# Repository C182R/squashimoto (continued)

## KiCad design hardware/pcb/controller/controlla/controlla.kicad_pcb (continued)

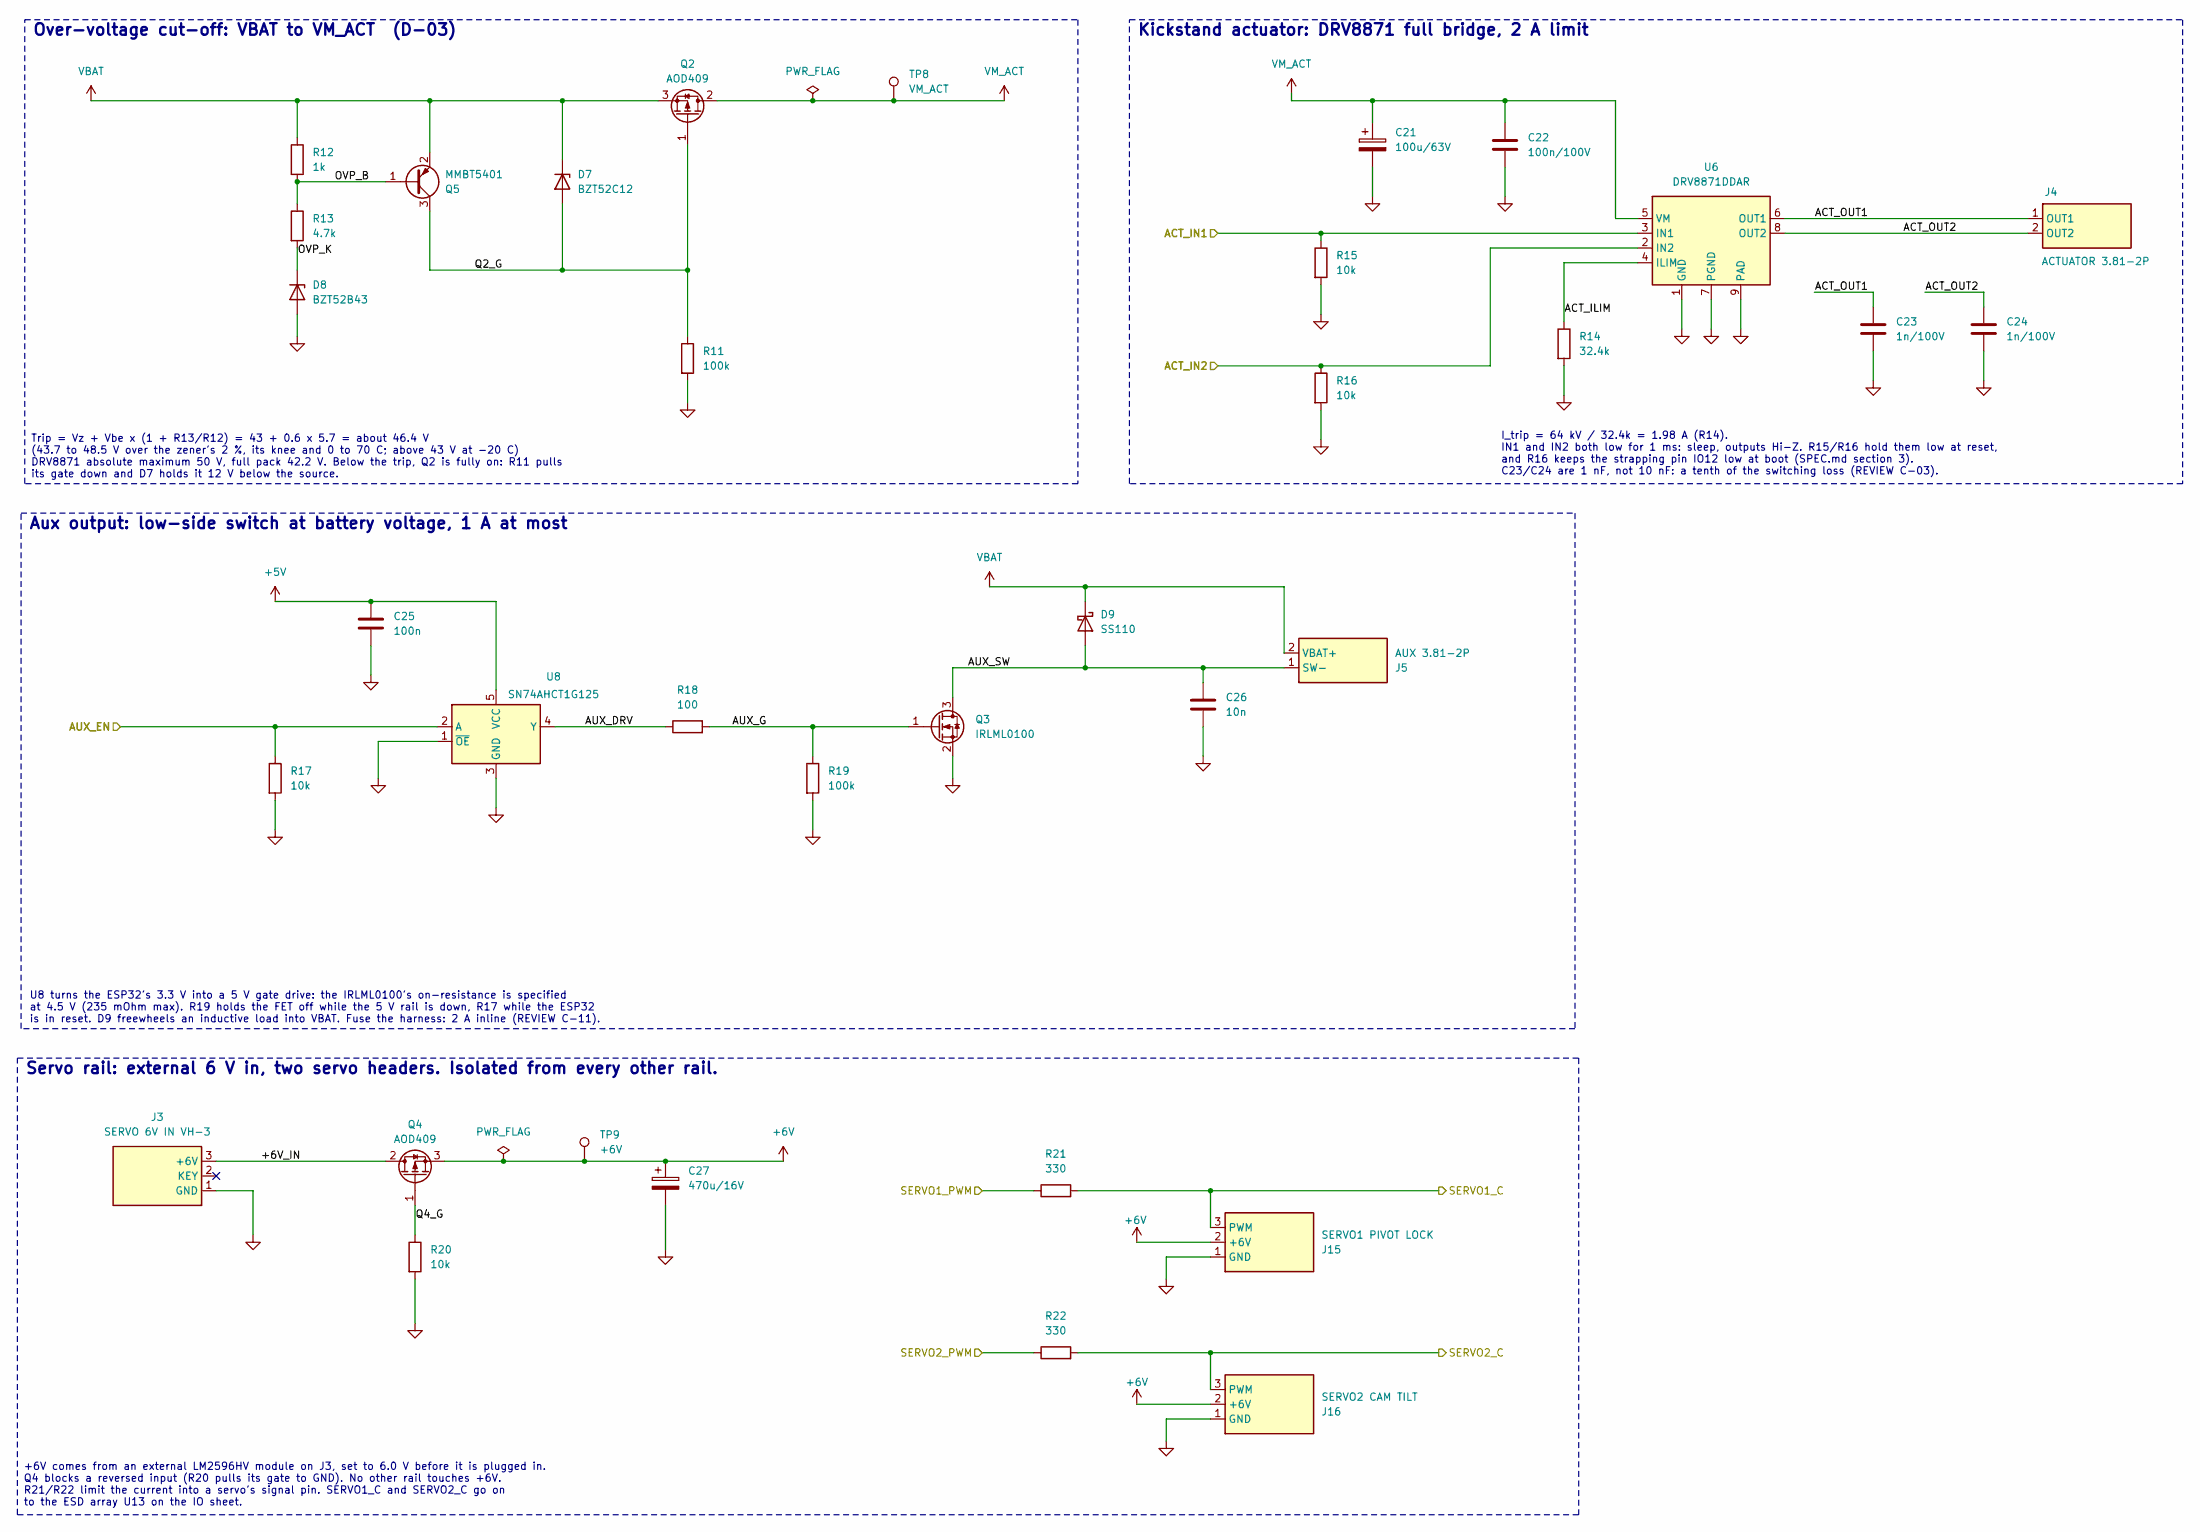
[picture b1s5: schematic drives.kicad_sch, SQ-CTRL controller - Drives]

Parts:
C21: 100u/63V; CP_Radial_D8.0mm_P3.50mm; MPN 63ZLH100MEFC8X16; LCSC C88747
C22: 100n/100V; C_0603_1608Metric; MPN TCC0603X7R104K101CT; LCSC C696916
C23, C24: 1n/100V; C_0603_1608Metric; MPN CC0603KRX7R0BB102; LCSC C106247
C25: 100n; C_0603_1608Metric; MPN CC0603KRX7R9BB104; LCSC C14663
C26: 10n; C_0603_1608Metric; MPN CC0603KRX7R0BB103; LCSC C107059
C27: 470u/16V; CP_Radial_D8.0mm_P3.50mm; MPN SHG470UF16V03EC0549; LCSC C2943989
D7: BZT52C12; D_SOD-123; MPN BZT52C12; LCSC C173429
D8: BZT52B43; D_SOD-123; MPN BZT52B43; LCSC C699127
D9: SS110; D_SMA; MPN SS110; LCSC C2482
J3: SERVO 6V IN VH-3; JST_VH_B3P-VH_1x03_P3.96mm_Vertical; MPN B3P-VH(LF)(SN); LCSC C160316
J4: ACTUATOR 3.81-2P; PhoenixContact_MC_1,5_2-G-3.81_1x02_P3.81mm_Horizontal; MPN KF2EDGR-3.81-2P; LCSC C441182
J5: AUX 3.81-2P; PhoenixContact_MC_1,5_2-G-3.81_1x02_P3.81mm_Horizontal; MPN KF2EDGR-3.81-2P; LCSC C441182
J15: SERVO1 PIVOT LOCK; PinHeader_1x03_P2.54mm_Vertical; MPN KH-2.54PH180-1X3P-L11.5; LCSC C2932698
J16: SERVO2 CAM TILT; PinHeader_1x03_P2.54mm_Vertical; MPN KH-2.54PH180-1X3P-L11.5; LCSC C2932698
Q2, Q4: AOD409; TO-252-2; MPN AOD409; LCSC C36220
Q3: IRLML0100; SOT-23; MPN IRLML0100TRPBF; LCSC C53658
Q5: MMBT5401; SOT-23; MPN MMBT5401(RANGE:200-300); LCSC C8326
R11, R19: 100k; R_0603_1608Metric; MPN 0603WAF1003T5E; LCSC C25803
R12: 1k; R_0603_1608Metric; MPN 0603WAF1001T5E; LCSC C21190
R13: 4.7k; R_0603_1608Metric; MPN 0603WAF4701T5E; LCSC C23162
R14: 32.4k; R_0603_1608Metric; MPN 0603WAF3242T5E; LCSC C13187
R15, R16, R17, R20: 10k; R_0603_1608Metric; MPN 0603WAF1002T5E; LCSC C25804
R18: 100; R_0603_1608Metric; MPN 0603WAF1000T5E; LCSC C22775
R21, R22: 330; R_0603_1608Metric; MPN 0603WAF3300T5E; LCSC C23138
TP8: VM_ACT; TestPoint_Pad_D1.5mm
TP9: +6V; TestPoint_Pad_D1.5mm
U6: DRV8871DDAR; HSOP-8-1EP_3.9x4.9mm_P1.27mm_EP2.41x3.1mm; MPN DRV8871DDAR; LCSC C75864
U8: SN74AHCT1G125; SOT-23-5; MPN SN74AHCT1G125DBVR; LCSC C7484

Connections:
+5V: C25.1, U8.5 (VCC); also elsewhere on the board
+6V: C27.1, J15.2 (+6V), J16.2 (+6V), Q4.3 (S), TP9.1 (1_1)
/MCU/ACT_IN1: R15.1, U6.3 (IN1); also elsewhere on the board
/MCU/ACT_IN2: R16.1, U6.2 (IN2); also elsewhere on the board
/MCU/AUX_EN: R17.1, U8.2 (A); also elsewhere on the board
/MCU/SERVO1_PWM: R21.1; also elsewhere on the board
/MCU/SERVO2_PWM: R22.1; also elsewhere on the board
/drives/+6V_IN: J3.3 (+6V), Q4.2 (D)
/drives/ACT_ILIM: R14.1, U6.4 (ILIM)
/drives/ACT_OUT1: C23.1, J4.1 (OUT1), U6.6 (OUT1)
/drives/ACT_OUT2: C24.1, J4.2 (OUT2), U6.8 (OUT2)
/drives/AUX_DRV: R18.1, U8.4 (Y)
/drives/AUX_G: Q3.1 (G), R18.2, R19.1
/drives/AUX_SW: C26.1, D9.2 (A), J5.1 (SW-), Q3.3 (D)
/drives/OVP_B: Q5.1 (B), R12.2, R13.1
/drives/OVP_K: D8.1 (K), R13.2
/drives/Q2_G: D7.2 (A), Q2.1 (G), Q5.3 (C), R11.1
/drives/Q4_G: Q4.1 (G), R20.1
/drives/SERVO1_C: J15.3 (PWM), R21.2; also elsewhere on the board
/drives/SERVO2_C: J16.3 (PWM), R22.2; also elsewhere on the board
GND: C21.2, C22.2, C23.2, C24.2, C25.2, C26.2, C27.2, D8.2 (A), J3.1 (GND), J15.1 (GND), J16.1 (GND), Q3.2 (S), R11.2, R14.2, R15.2, R16.2, R17.2, R19.2, R20.2, U6.1 (GND), U6.7 (PGND), U6.9 (PAD), U8.1 (~OE), U8.3 (GND); also elsewhere on the board
VBAT: D7.1 (K), D9.1 (K), J5.2 (VBAT+), Q2.3 (S), Q5.2 (E), R12.1; also elsewhere on the board
VM_ACT: C21.1, C22.1, Q2.2 (D), TP8.1 (1_1), U6.5 (VM)

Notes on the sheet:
Servo rail: external 6 V in, two servo headers. Isolated from every other rail.
Aux output: low-side switch at battery voltage, 1 A at most
I_trip = 64 kV / 32.4k = 1.98 A (R14). IN1 and IN2 both low for 1 ms: sleep, outputs Hi-Z. R15/R16 hold them low at reset, and R16 keeps the strapping pin IO12 low at boot (SPEC.md section 3). C23/C24 are 1 nF, not 10 nF: a tenth of the switching loss (REVIEW C-03).
Kickstand actuator: DRV8871 full bridge, 2 A limit
U8 turns the ESP32's 3.3 V into a 5 V gate drive: the IRLML0100's on-resistance is specified at 4.5 V (235 mOhm max). R19 holds the FET off while the 5 V rail is down, R17 while the ESP32 is in reset. D9 freewheels an inductive load into VBAT. Fuse the harness: 2 A inline (REVIEW C-11).
Trip = Vz + Vbe x (1 + R13/R12) = 43 + 0.6 x 5.7 = about 46.4 V (43.7 to 48.5 V over the zener's 2 %, its knee and 0 to 70 C; above 43 V at -20 C) DRV8871 absolute maximum 50 V, full pack 42.2 V. Below the trip, Q2 is fully on: R11 pulls its gate down and D7 holds it 12 V below the source.
Over-voltage cut-off: VBAT to VM_ACT (D-03)
+6V comes from an external LM2596HV module on J3, set to 6.0 V before it is plugged in. Q4 blocks a reversed input (R20 pulls its gate to GND). No other rail touches +6V. R21/R22 limit the current into a servo's signal pin. SERVO1_C and SERVO2_C go on to the ESD array U13 on the IO sheet.

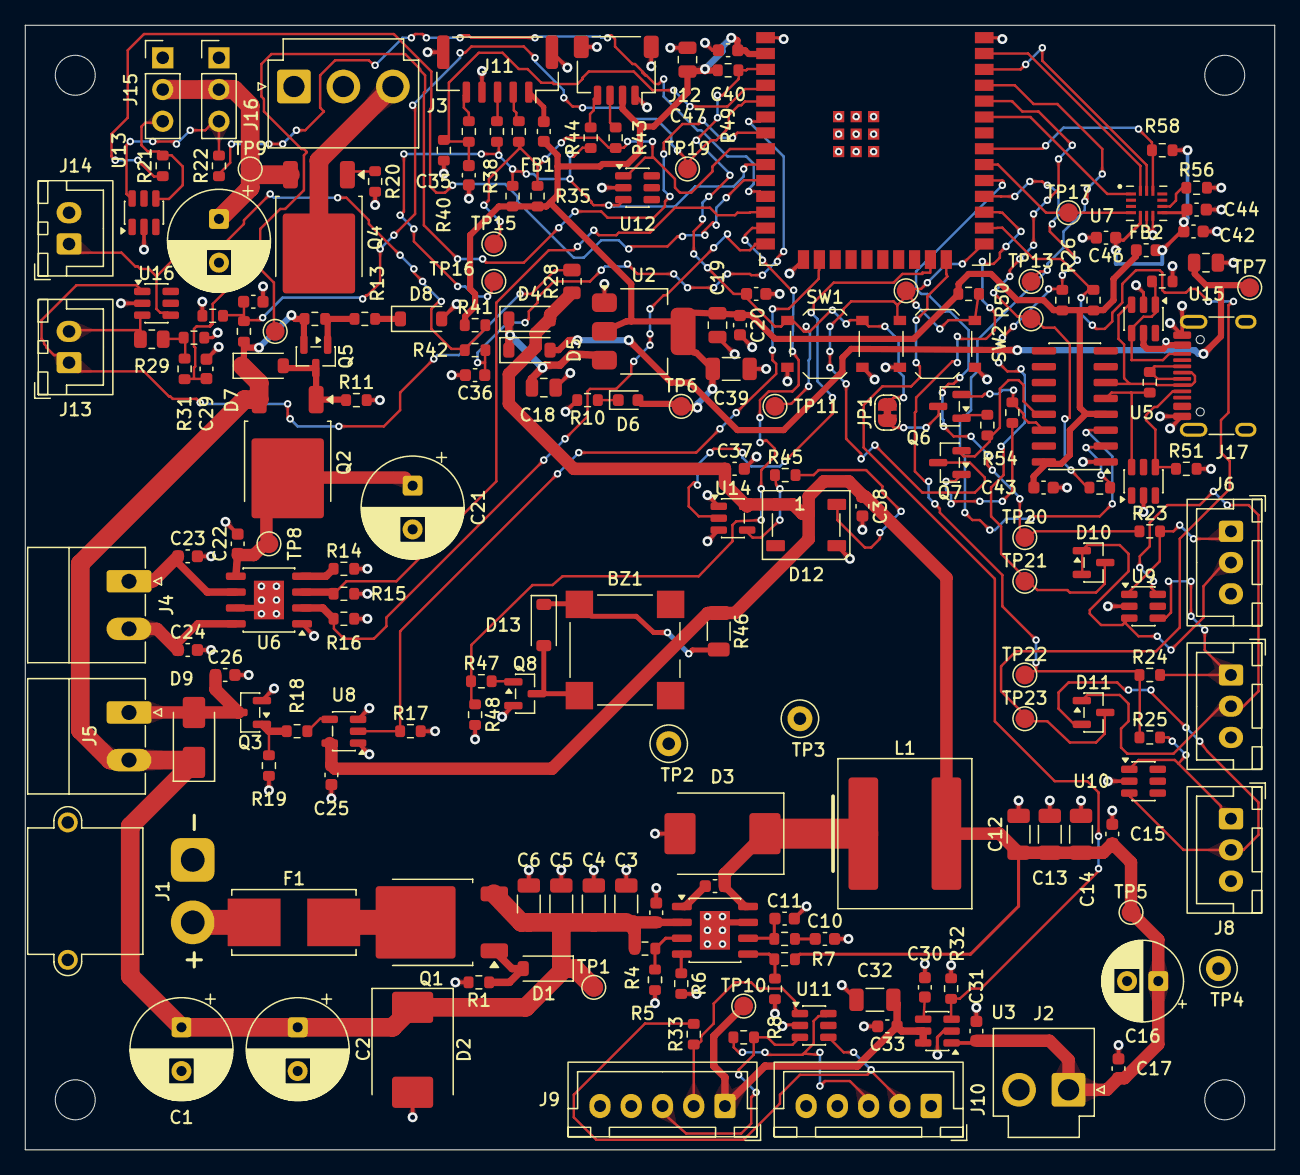
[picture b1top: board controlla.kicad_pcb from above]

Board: 4 copper layers, 100.0 x 90.0 mm, 193 parts (0 on the bottom side), 100 nets.

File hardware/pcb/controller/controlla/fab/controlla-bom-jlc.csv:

"Comment","Designator","Footprint","LCSC Part #"
"MLT-8530","BZ1","squashimoto:Buzzer_Huaneng_MLT-8530","C94599"
"100u/63V","C1,C2,C21","squashimoto:CP_Radial_D8.0mm_P3.50mm","C88747"
"2.2u/100V","C3,C4,C5,C6","squashimoto:C_1206_3216Metric","C577211"
"100n/100V","C7,C22","squashimoto:C_0603_1608Metric","C696916"
"100n","C8,C9,C15,C17,C20,C25,C29,C33,C36,C37,C38,C40,C43,C44","squashimoto:C_0603_1608Metric","C14663"
"10n","C10,C26,C35,C46","squashimoto:C_0603_1608Metric","C107059"
"100p","C11","squashimoto:C_0603_1608Metric","C14858"
"22u","C12,C13,C14,C32,C39","squashimoto:C_1206_3216Metric","C12891"
"470u/10V poly","C16","squashimoto:CP_Radial_D6.3mm_P2.50mm","C698160"
"10u","C18,C19,C42,C47","squashimoto:C_0805_2012Metric","C15850"
"1n/100V","C23,C24","squashimoto:C_0603_1608Metric","C106247"
"470u/16V","C27","squashimoto:CP_Radial_D8.0mm_P3.50mm","C2943989"
"2.2n","C30","squashimoto:C_0603_1608Metric","C16033"
"1u","C31,C41","squashimoto:C_0603_1608Metric","C15849"
"2.2u","C45","squashimoto:C_0603_1608Metric","C23630"
"BZT52C12","D1,D7","squashimoto:D_SOD-123","C173429"
"SMDJ45A","D2","squashimoto:D_SMC","C49066976"
"SK1010C","D3","squashimoto:D_SMC","C65020"
"B5819W","D4,D5","squashimoto:D_SOD-123","C64885"
"red","D6","squashimoto:LED_0603_1608Metric","C2286"
"BZT52B43","D8","squashimoto:D_SOD-123","C699127"
"SS110","D9","squashimoto:D_SMA","C2482"
"BAT54A","D10,D11","squashimoto:SOT-23","C181199"
"WS2812B","D12","squashimoto:LED_WS2812B_PLCC4_5.0x5.0mm_P3.2mm","C2843785"
"1N4148W","D13","squashimoto:D_SOD-123","C81598"
"7A 0154007.DRT","F1","squashimoto:Fuseholder_Littelfuse_Nano2_154x","C2760740"
"600R","FB1,FB2","squashimoto:L_0603_1608Metric","C19330"
"XT30PW-M","J1","squashimoto:AMASS_XT30PW-M_1x02_P2.50mm_Horizontal","C431092"
"PI 5V VH-2","J2","squashimoto:JST_VH_B2P-VH_1x02_P3.96mm_Vertical","C160315"
"SERVO 6V IN VH-3","J3","squashimoto:JST_VH_B3P-VH_1x03_P3.96mm_Vertical","C160316"
"ACTUATOR 3.81-2P,AUX 3.81-2P","J4,J5","squashimoto:PhoenixContact_MC_1,5_2-G-3.81_1x02_P3.81mm_Horizontal","C441182"
"UART FRONT L,UART FRONT R,UART REAR","J6,J7,J8","squashimoto:JST_XH_B3B-XH-A_1x03_P2.50mm_Vertical","C144394"
"LIDAR USB ADAPTER XH-5,LIDAR XH-5","J9,J10","squashimoto:JST_XH_B5B-XH-A_1x05_P2.50mm_Vertical","C157991"
"ENCODER GH-5","J11","squashimoto:JST_GH_SM05B-GHS-TB_1x05-1MP_P1.25mm_Horizontal","C189896"
"I2C SPARE SH-4","J12","squashimoto:JST_SH_SM04B-SRSS-TB_1x04-1MP_P1.00mm_Horizontal","C160404"
"BATT NTC 10k,E-STOP NC","J13,J14","squashimoto:JST_XH_B2B-XH-A_1x02_P2.50mm_Vertical","C158012"
"SERVO1 PIVOT LOCK,SERVO2 CAM TILT","J15,J16","squashimoto:PinHeader_1x03_P2.54mm_Vertical","C2932698"
"USB-C TYPE-C-31-M-12","J17","squashimoto:USB_C_Receptacle_HRO_TYPE-C-31-M-12","C165948"
"10uH XAL1010","L1","squashimoto:L_Coilcraft_XAL1010-XXX","C6358489"
"AOD409","Q1,Q2,Q4","squashimoto:TO-252-2","C36220"
"IRLML0100","Q3","squashimoto:SOT-23","C53658"
"MMBT5401","Q5","squashimoto:SOT-23","C8326"
"SS8050","Q6,Q7","squashimoto:SOT-23","C2150"
"AO3400A","Q8","squashimoto:SOT-23","C20917"
"100k","R1,R2,R11,R19,R39","squashimoto:R_0603_1608Metric","C25803"
"5.1k","R3,R51,R52","squashimoto:R_0603_1608Metric","C23186"
"732k","R4","squashimoto:R_0603_1608Metric","C23239"
"33.2k","R5","squashimoto:R_0603_1608Metric","C23003"
"240k","R6","squashimoto:R_0603_1608Metric","C4197"
"53.6k","R7","squashimoto:R_0603_1608Metric","C23074"
"10k","R8,R15,R16,R17,R20,R31,R32,R48,R49,R50,R54,R55,R56,R58","squashimoto:R_0603_1608Metric","C25804"
"16.2k","R9","squashimoto:R_0603_1608Metric","C22885"
"1k","R10,R12,R23,R24,R25,R30,R42","squashimoto:R_0603_1608Metric","C21190"
"4.7k","R13,R26,R27","squashimoto:R_0603_1608Metric","C23162"
"32.4k","R14","squashimoto:R_0603_1608Metric","C13187"
"100","R18,R37,R38,R43,R44,R47","squashimoto:R_0603_1608Metric","C22775"
"330","R21,R22,R45","squashimoto:R_0603_1608Metric","C23138"
"330","R28,R29","squashimoto:R_0805_2012Metric","C17630"
"470","R33,R53","squashimoto:R_0603_1608Metric","C23179"
"2.2k","R34,R35,R36","squashimoto:R_0603_1608Metric","C4190"
"220k","R40","squashimoto:R_0603_1608Metric","C22961"
"20k","R41","squashimoto:R_0603_1608Metric","C4184"
"10","R46","squashimoto:R_1206_3216Metric","C17903"
"0","R59","squashimoto:R_0603_1608Metric","C21189"
"BOOT,RESET","SW1,SW2","squashimoto:SW_Push_1P1T_XKB_TS-1187A","C318884"
"TPS54360BDDAR","U1","squashimoto:HSOP-8-1EP_3.9x4.9mm_P1.27mm_EP2.41x3.1mm","C524806"
"AP7361C-33ER-13","U2","squashimoto:SOT-223-3_TabPin2","C3743528"
"TPS22918DBVR","U3","squashimoto:SOT-23-6","C131941"
"ESP32-WROOM-32E-N4","U4","squashimoto:ESP32-WROOM-32E","C701341"
"CH340C","U5","squashimoto:SOIC-16_3.9x9.9mm_P1.27mm","C84681"
"DRV8871DDAR","U6","squashimoto:HSOP-8-1EP_3.9x4.9mm_P1.27mm_EP2.41x3.1mm","C75864"
"ICM-42688-P","U7","squashimoto:LGA-14_3x2.5mm_P0.5mm_ICM-42688-P","C54308212"
"SN74AHCT1G125","U8,U14","squashimoto:SOT-23-5","C7484"
"SRV05-4","U9,U10,U11,U12,U13,U15,U16,U17","squashimoto:SOT-23-6","C558418"

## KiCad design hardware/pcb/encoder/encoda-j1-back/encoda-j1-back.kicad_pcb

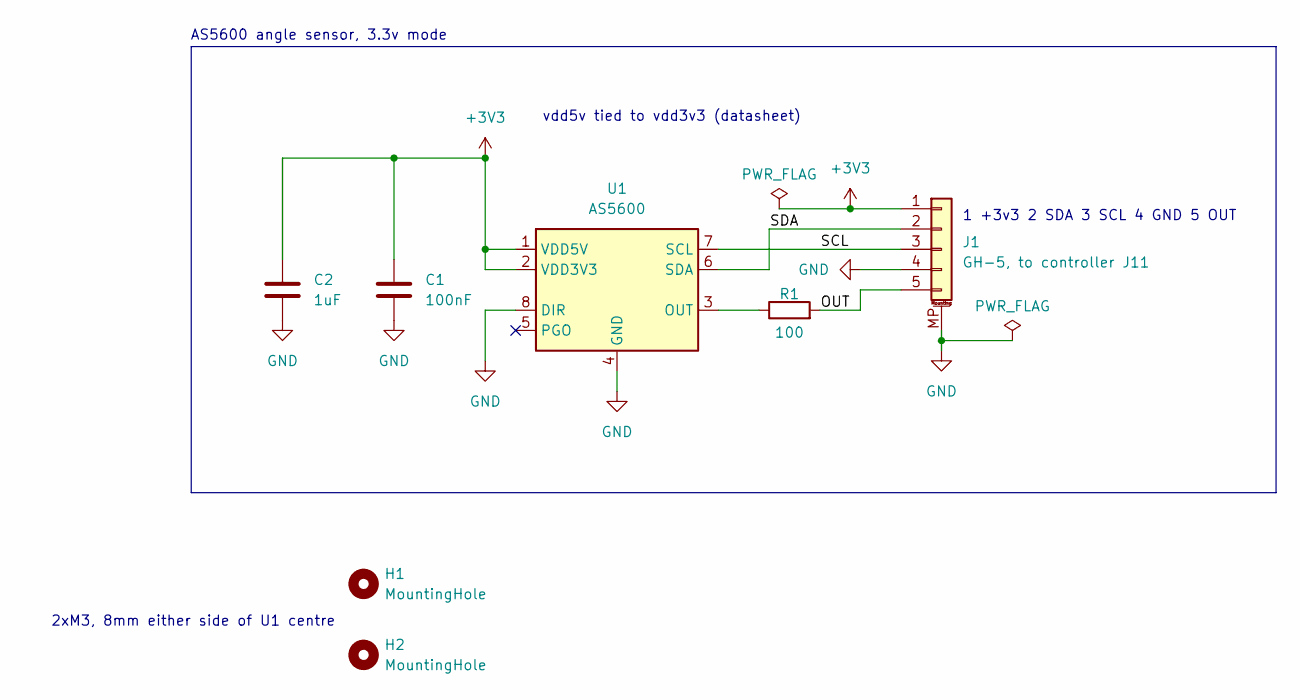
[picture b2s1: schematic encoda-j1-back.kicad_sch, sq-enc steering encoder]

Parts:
C1: 100nF; C_0603_1608Metric; MPN CC0603JRX7R9BB104; LCSC C91183
C2: 1uF; C_0603_1608Metric; MPN CL10A105KA8NNNC; LCSC C5673
H1, H2: MountingHole; MountingHole_3.2mm_M3
J1: GH-5, to controller J11; JST_GH_SM05B-GHS-TB_1x05-1MP_P1.25mm_Horizontal; MPN SM05B-GHS-TB(LF)(SN); LCSC C189896
R1: 100; R_0603_1608Metric; MPN 0603WAF1000T5E; LCSC C22775
U1: AS5600; SOIC-8_3.9x4.9mm_P1.27mm; MPN AS5600-ASOT-SOIC8; LCSC C55240803

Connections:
+3V3: C1.1, C2.1, J1.1, U1.1 (VDD5V), U1.2 (VDD3V3)
/OUT: J1.5, R1.2
/SCL: J1.3, U1.7 (SCL)
/SDA: J1.2, U1.6 (SDA)
GND: C1.2, C2.2, J1.4, J1.MP (MountPin), U1.4 (GND), U1.8 (DIR)
unnamed: R1.1, U1.3 (OUT)

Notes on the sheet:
2xM3, 8mm either side of U1 centre
AS5600 angle sensor, 3.3v mode
1 +3v3 2 SDA 3 SCL 4 GND 5 OUT
vdd5v tied to vdd3v3 (datasheet)

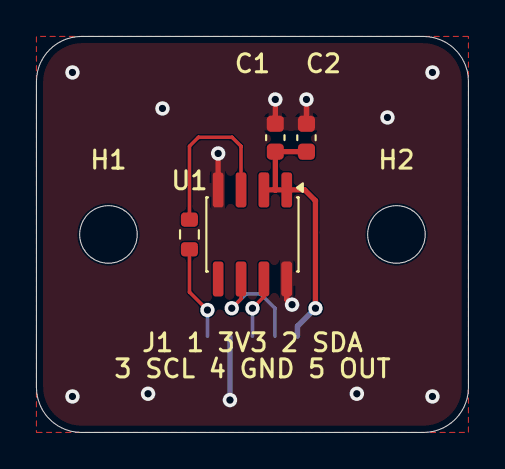
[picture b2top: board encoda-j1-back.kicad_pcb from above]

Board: 2 copper layers, 24.0 x 22.0 mm, 7 parts (1 on the bottom side), 6 nets.
